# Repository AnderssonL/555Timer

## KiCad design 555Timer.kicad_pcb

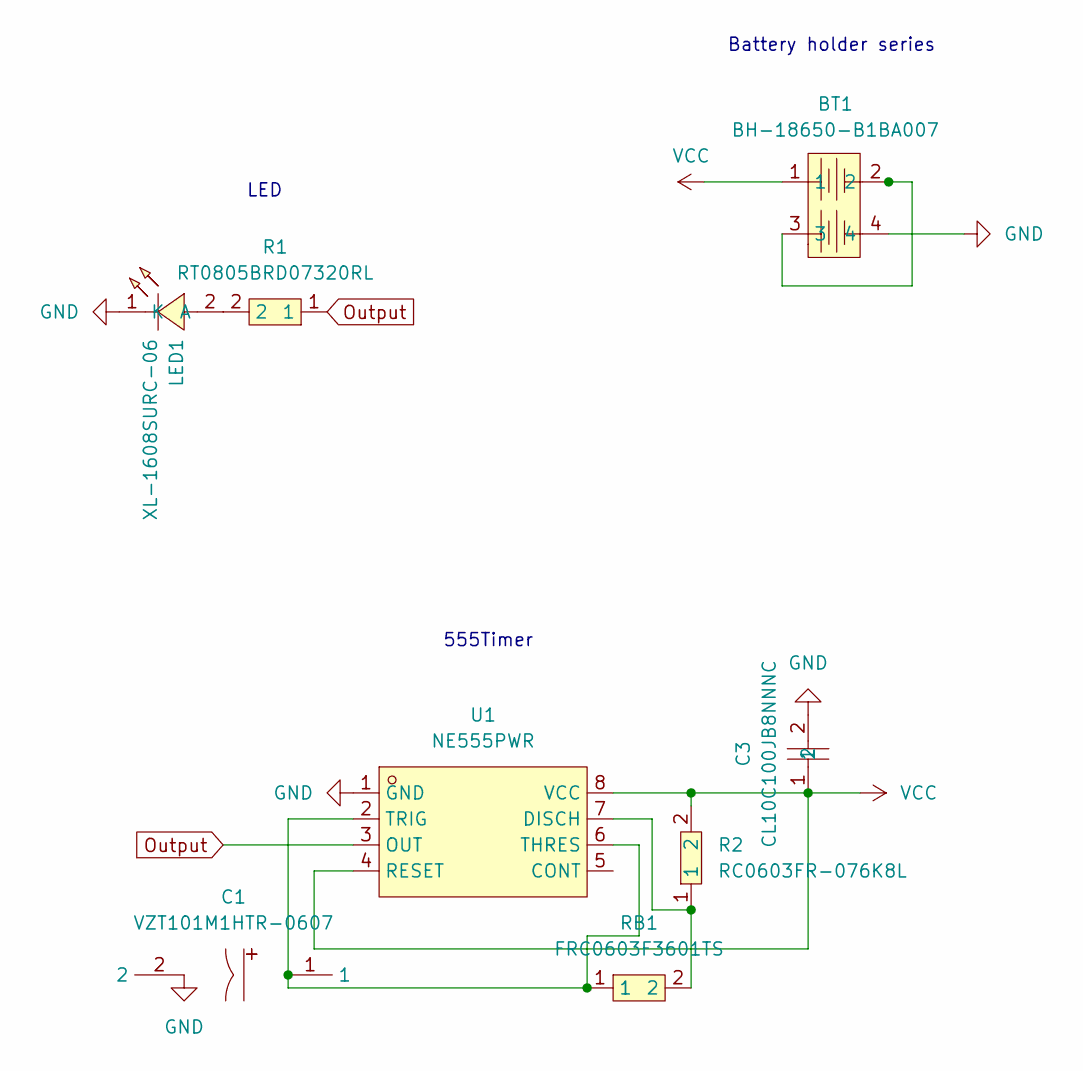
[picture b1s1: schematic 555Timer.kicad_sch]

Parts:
BT1: BH-18650-B1BA007; BAT-SMD_BH-18650-B1BA007; LCSC Part C6937126
C1: VZT101M1HTR-0607; CAP-SMD_BD6.3-L6.6-W6.6-RD; LCSC Part C311622
C3: CL10C100JB8NNNC; C0603; LCSC Part C1634
LED1: XL-1608SURC-06; LED0603-RD_RED; LCSC Part C965799
R1: RT0805BRD07320RL; R0805; LCSC Part C865402
R2: RC0603FR-076K8L; R0603; LCSC Part C114632
RB1: FRC0603F3601TS; R0603; LCSC Part C2933208
U1: NE555PWR; TSSOP-8_L4.4-W3.0-P0.65-LS6.4-BL; LCSC Part C105643

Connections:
GND: BT1.4, C1.2, C3.2, LED1.1 (K), U1.1 (GND)
unnamed: BT1.2, BT1.3
unnamed: LED1.2 (A), R1.2
unnamed: R2.1, RB1.2, U1.7 (DISCH)
unnamed: C1.1, RB1.1, U1.2 (TRIG), U1.6 (THRES)
Output: R1.1, U1.3 (OUT)
VCC: BT1.1, C3.1, R2.2, U1.4 (RESET), U1.8 (VCC)

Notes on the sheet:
LED
Battery holder series
555Timer

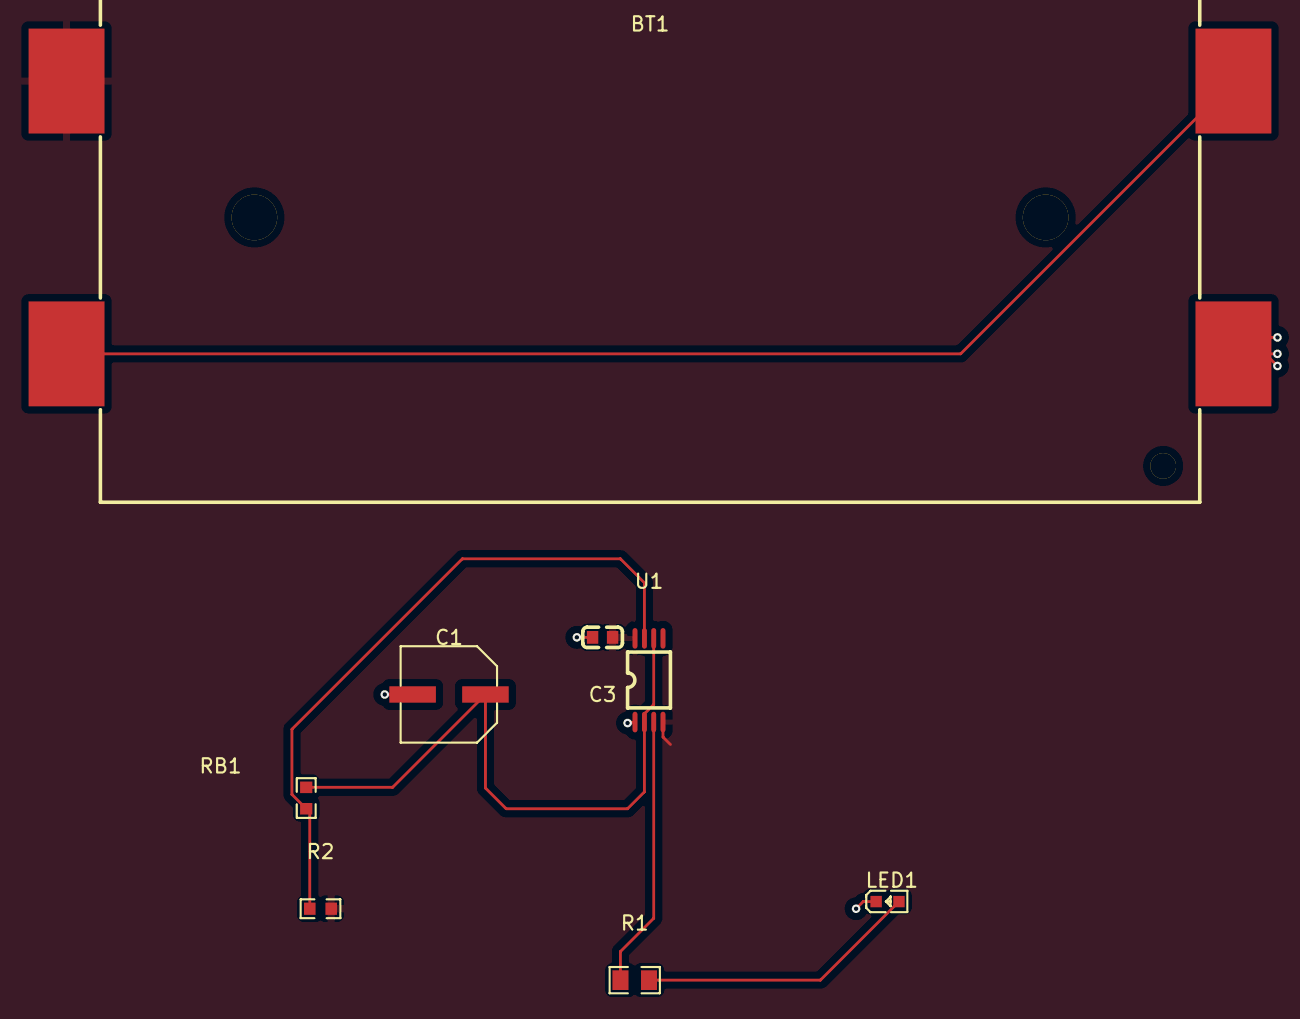
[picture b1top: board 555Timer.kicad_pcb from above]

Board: 2 copper layers, 8 parts (0 on the bottom side), 7 nets.

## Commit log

2025-09-24 added PDF
2025-09-24 changed
2025-09-25 updated plot
2025-09-25 made tracing
2025-09-25 changed after soproni feedback
